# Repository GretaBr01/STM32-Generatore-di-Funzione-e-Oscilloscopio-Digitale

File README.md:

# STM32 Generatore di Funzione e Oscilloscopio Digitale

Progetto per Nucleo STM32 che implementa un generatore di funzioni DAC e un semplice oscilloscopio su display SSD1306.

## Panoramica
- Generatore di forme d'onda (seno, rettangolare, triangolare, saw) utilizzando DAC.
    - Funzioni principali: [`initOut`](outsetting.c), [`startOut`](outsetting.c), [`setShape`](outsetting.h).
- Acquisizione ADC campiona il segnale e alimenta il buffer per lo scope.
  - Funzioni principali: [`startADCThread`](sampler.c), [`updateScope`](sampler.c).
- Visualizzazione su OLED (SSD1306).
  - Driver e API: [ssd1306/ssd1306.h](ssd1306/ssd1306.h), implementazione [ssd1306/ssd1306.c](ssd1306/ssd1306.c). Font: [ssd1306/ssd1306_font.c](ssd1306/ssd1306_font.c), [ssd1306/ssd1306_font_7_10.c](ssd1306/ssd1306_font_7_10.c).
  - Interfaccia alto livello: [`startOledThread`](oled_manager.c), [`oledUpdateScope`](oled_manager.h).
- Gestione encoder rotativo e pulsante.
  - Funzioni: [`startEncoderThread`](encoder_manager.c), [`getEncoderCount`](encoder_manager.c), [`isEncoderButtonPressed`](encoder_manager.c).

## File principali
- [main.c](main.c) — nodo di avvio, gestione pulsante on/off e thread LED.
- [Makefile](Makefile) — build system (ChibiOS + HAL + ssd1306).
- [outsetting.c](outsetting.c), [outsetting.h](outsetting.h) — generatore DAC e configurazione.
- [sampler.c](sampler.c), [sampler.h](sampler.h) — acquisizione ADC e buffer scope.
- [oled_manager.c](oled_manager.c), [oled_manager.h](oled_manager.h) — logica menu e disegno su display.
- [encoder_manager.c](encoder_manager.c), [encoder_manager.h](encoder_manager.h) — lettura encoder e pulsante.
- [ssd1306/ssd1306.c](ssd1306/ssd1306.c), [ssd1306/ssd1306.h](ssd1306/ssd1306.h) — driver SSD1306 e helper.
- [ssd1306/ssd1306_font.c](ssd1306/ssd1306_font.c), [ssd1306/ssd1306_font_7_10.c](ssd1306/ssd1306_font_7_10.c) — dati font.
- [cfg/halconf.h](cfg/halconf.h), [cfg/chconf.h](cfg/chconf.h), [cfg/mcuconf.h](cfg/mcuconf.h) — configurazioni ChibiOS/HAL.

## Hardware
- STM32 Nucleo-64 ST_NUCLEO64_G474RE.
- Display OLED SSD1306 128x64.
- LED RGB.
- Encoder rotante con pulsante.
- Pulsante ON/OFF.

## Mappatura pin
Di seguito sono riportati i pin definiti nel codice (o suggeriti come mapping comune). Verificare sempre i file sorgente (outsetting.c, sampler.c, encoder_manager.c, main.c) e adattare al cablaggio reale.

- I2C (SSD1306)
  - SCL → PB8
  - SDA → PB9

- LED (definiti in main.c)
  - R LED → PB10
  - G LED → PA8
  - B LED → PA9

- Pulsante ON/OFF (definito in main.c)
  - BUTTON ON/OFF → PC7 
  - Nota: input pull-up, evento su entrambi i fronti

- DAC (uscita generatore)
  - DAC OUT1 → PA4  (DAC1_OUT1)
  - Nota: mapping comune, verificare outsetting.c

- ADC (ingresso oscilloscopio)
  - ADC IN (scope input) → PA0 (ADC_IN1)
  - Nota: adattare a sampler.c

- Encoder
  - ENC_CLK →  PB5
  - ENC_DT  →  PB3
  - ENC_SW  →  PB4
  - Nota: i pin effettivi sono definiti in encoder_manager.h;

## Uso
- Premere pulsante ON/OFF per attivare/disattivare sistema.
- Quando acceso, i thread vengono avviati automaticamente:
  - initOut(), startOut() => DAC
  - startADCThread() => campionamento ADC
  - startOledThread() => GUI OLED
  - startEncoderThread() => controllo menu
- Ruotare l'encoder e premere il pulsante encoder per navigare il menu su OLED.

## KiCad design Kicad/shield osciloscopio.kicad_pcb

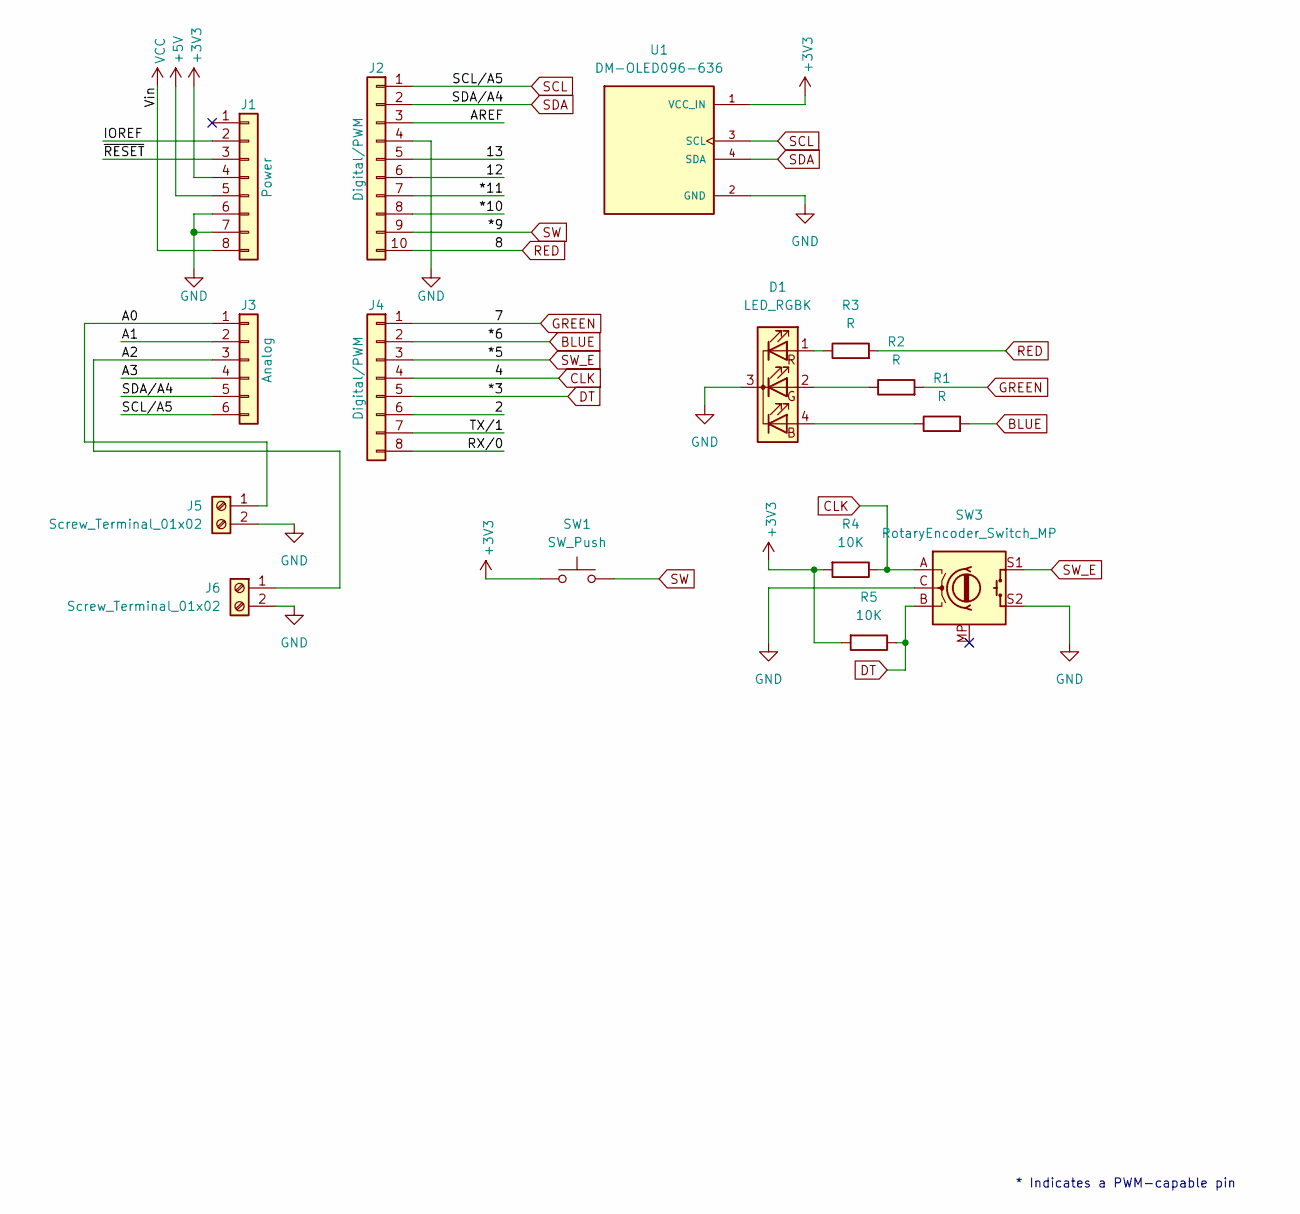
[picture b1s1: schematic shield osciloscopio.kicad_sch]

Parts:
D1: LED_RGBK; LED_D5.0mm-4_RGB
J1: Power; PinHeader_1x08_P2.54mm_Vertical
J2: Digital/PWM; PinHeader_1x10_P2.54mm_Vertical
J3: Analog; PinHeader_1x06_P2.54mm_Vertical
J4: Digital/PWM; PinHeader_1x08_P2.54mm_Vertical
J5, J6: Screw_Terminal_01x02; TE_282837-2
R1, R2, R3: R; R_Axial_DIN0309_L9.0mm_D3.2mm_P15.24mm_Horizontal
R4, R5: 10K; R_0805_2012Metric
SW1: SW_Push; SW_PUSH_6mm
SW3: RotaryEncoder_Switch_MP; RotaryEncoder_Alps_EC11E-Switch_Vertical_H20mm
U1: DM-OLED096-636; MODULE_DM-OLED096-636; PARTREV 2018-09-10

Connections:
+3V3: J1.4, R4.2, R5.2, SW1.1, U1.1 (VCC_IN)
+5V: J1.5
/2: J4.6
/12: J2.6
/13: J2.5
/*10: J2.8
/*11: J2.7
/A0: J3.1, J5.1
/A1: J3.2
/A2: J3.3, J6.1
/A3: J3.4
/AREF: J2.3
/IOREF: J1.2
/RX/0: J4.8
/TX/1: J4.7
/~RESET: J1.3
BLUE: J4.2, R1.2
CLK: J4.4, R4.1, SW3.A
DT: J4.5, R5.1, SW3.B
GND: D1.3 (K), J1.6, J1.7, J2.4, J5.2, J6.2, SW3.C, SW3.S2, U1.2 (GND)
GREEN: J4.1, R2.2
unnamed: D1.4 (BA), R1.1
unnamed: D1.2 (GA), R2.1
unnamed: D1.1 (RA), R3.1
RED: J2.10, R3.2
SCL: J2.1, J3.6, U1.3 (SCL)
SDA: J2.2, J3.5, U1.4 (SDA)
SW: J2.9, SW1.2
SW_E: J4.3, SW3.S1
VCC: J1.8

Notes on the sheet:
* Indicates a PWM-capable pin

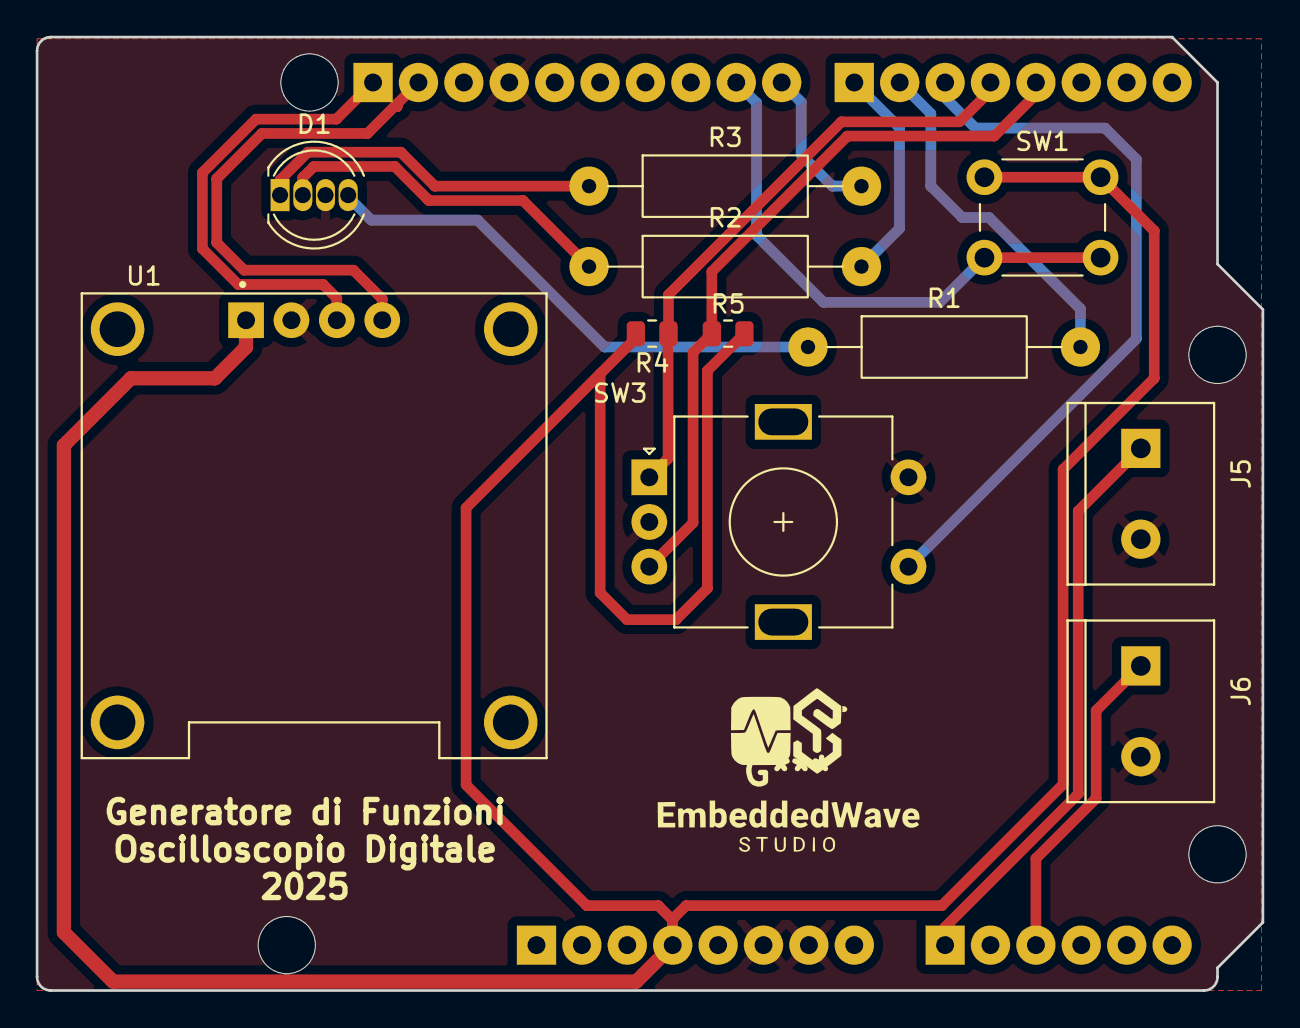
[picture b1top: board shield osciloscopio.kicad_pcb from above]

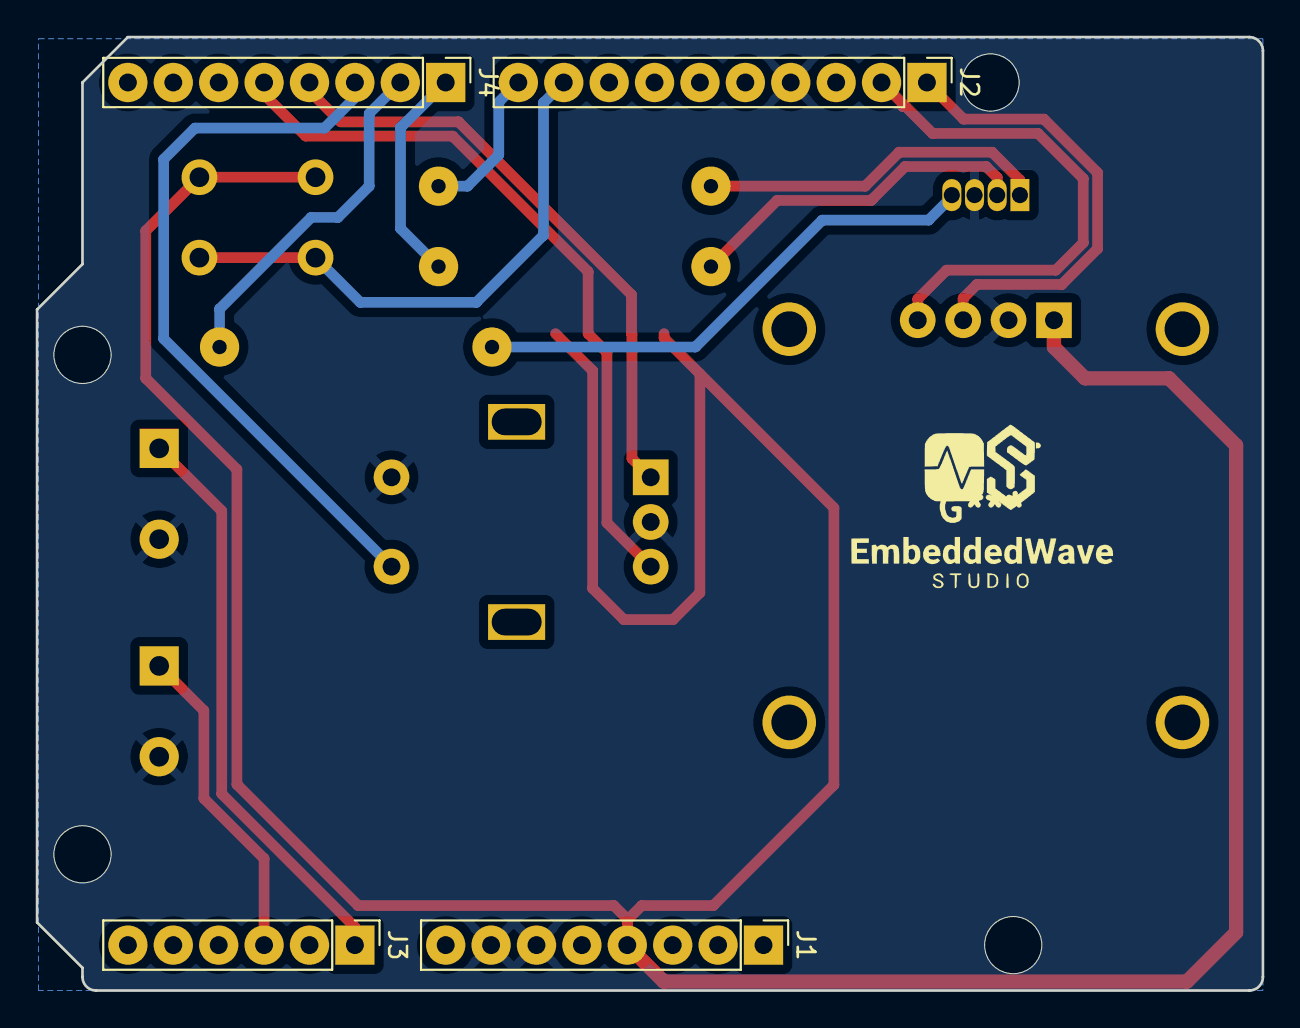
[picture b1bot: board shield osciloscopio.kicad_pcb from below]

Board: 2 copper layers, 68.6 x 53.3 mm, 19 parts (4 on the bottom side), 16 nets.

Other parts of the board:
MH1, MH2, MH3, MH4: MountingHole_3.2mm

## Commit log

2025-11-17 progetto NISC 2025
2025-11-23 aggiunta logica bottone e led per accensione
2025-11-23 readme
2025-11-26 Add Kicad Files
2025-11-26 Actualizacion OLED
2025-11-28 3D printed case design
2025-11-28 st nucleo g4 code
